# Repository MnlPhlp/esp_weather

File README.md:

# esp_weather
weather station powerd by an esp32 and rust.

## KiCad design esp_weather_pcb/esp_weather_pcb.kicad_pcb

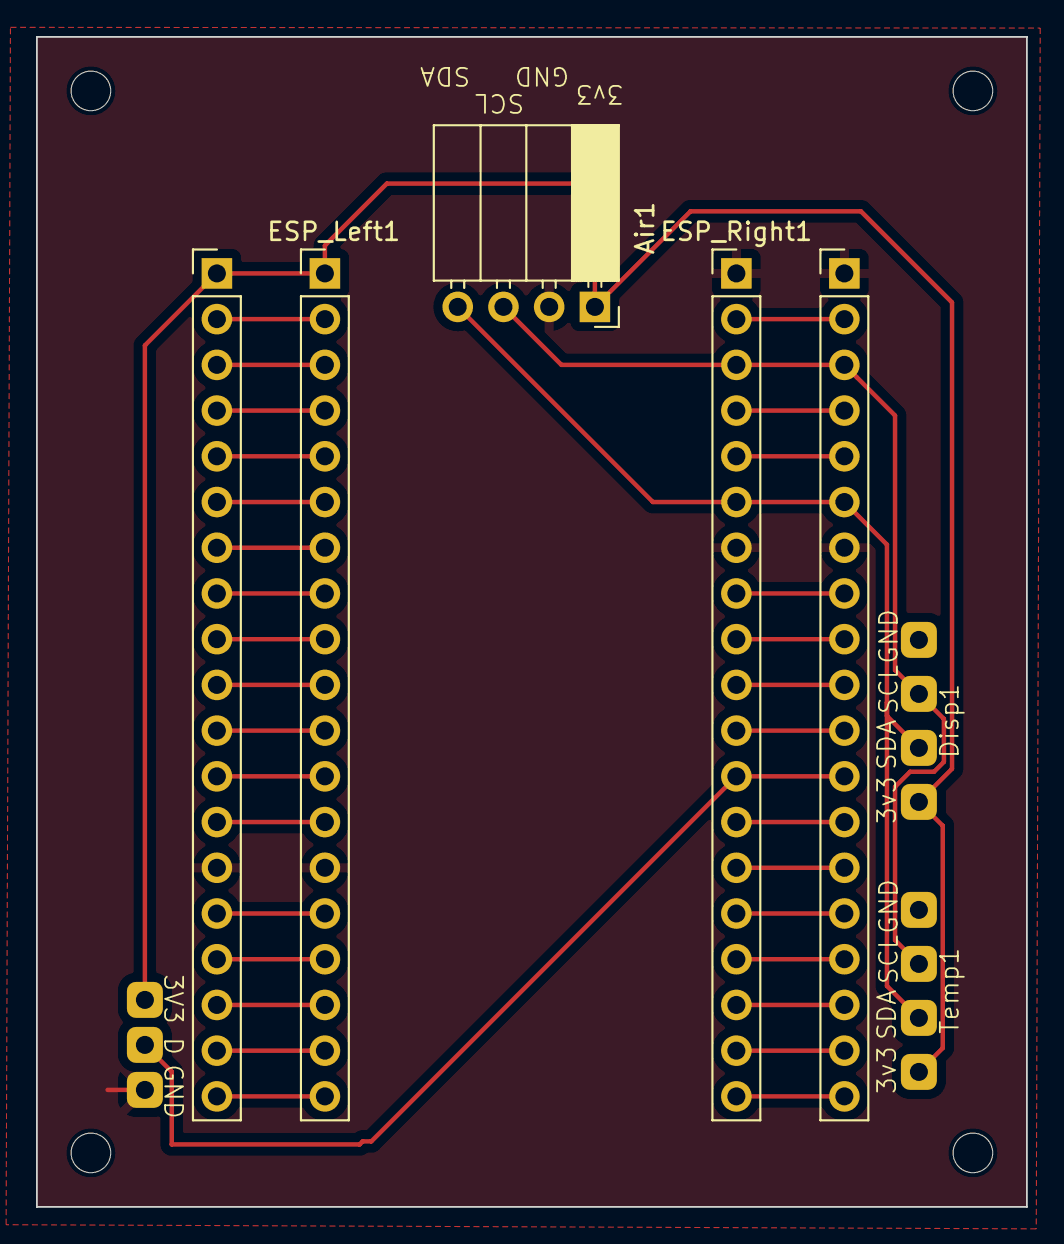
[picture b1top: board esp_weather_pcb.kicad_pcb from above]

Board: 2 copper layers, 55.0 x 65.0 mm, 8 parts (0 on the bottom side), 36 nets.

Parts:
Air1: PinSocket_1x04_P2.54mm_Horizontal
Disp1: I2C_Pads
ESP_Left1: esp32_38P_Left; esp32_38P_left
ESP_Right1: esp32_38P_Right; esp32_38P_right
Outside1: 3WIRE_Pads
Pads_Right1: esp32_38P_Right_Pads; esp32_38P_right_pads
Pads_left1: esp32_38P_Left_Pads; esp32_38P_left_Pads
Temp1: I2C_Pads

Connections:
3V3: Air1.1 (3V3), Disp1.1 (3V3), ESP_Left1.1 (3V3), Outside1.1 (3V3), Pads_left1.1 (3V3), Temp1.1 (3V3)
GND: Air1.2 (SDA), Disp1.4 (GND), ESP_Left1.14 (GND), ESP_Right1.32 (GND), ESP_Right1.38 (GND), Outside1.3 (GND), Pads_Right1.32 (GND), Pads_Right1.38 (GND), Pads_left1.14 (GND), Temp1.4 (GND)
unnamed: ESP_Left1.19 (5V), Pads_left1.19 (5V)
unnamed: ESP_Left1.2 (EN), Pads_left1.2 (EN)
unnamed: ESP_Left1.18 (FLASH_CMD), Pads_left1.18 (FLASH_CMD)
unnamed: ESP_Left1.16 (FLASH_D2), Pads_left1.16 (FLASH_D2)
unnamed: ESP_Left1.17 (FLASH_D3), Pads_left1.17 (FLASH_D3)
unnamed: ESP_Left1.13 (P12), Pads_left1.13 (P12)
unnamed: ESP_Left1.15 (P13), Pads_left1.15 (P13)
unnamed: ESP_Left1.12 (P14), Pads_left1.12 (P14)
unnamed: ESP_Left1.9 (P25), Pads_left1.9 (P25)
unnamed: ESP_Left1.10 (P26), Pads_left1.10 (P26)
unnamed: ESP_Left1.11 (P27), Pads_left1.11 (P27)
unnamed: ESP_Left1.7 (P32), Pads_left1.7 (P32)
unnamed: ESP_Left1.8 (P33), Pads_left1.8 (P33)
unnamed: ESP_Left1.5 (P34), Pads_left1.5 (P34)
unnamed: ESP_Left1.6 (P35), Pads_left1.6 (P35)
unnamed: ESP_Left1.3 (P36), Pads_left1.3 (P36)
unnamed: ESP_Left1.4 (P39), Pads_left1.4 (P39)
unnamed: ESP_Right1.20 (FLASH_CLK), Pads_Right1.20 (FLASH_CLK)
unnamed: ESP_Right1.21 (FLASH_D0), Pads_Right1.21 (FLASH_D0)
unnamed: ESP_Right1.22 (FLASH_D1), Pads_Right1.22 (FLASH_D1)
unnamed: ESP_Right1.25 (P0), Pads_Right1.25 (P0)
unnamed: ESP_Right1.24 (P2), Pads_Right1.24 (P2)
unnamed: ESP_Right1.26 (P4), Pads_Right1.26 (P4)
unnamed: ESP_Right1.29 (P5), Pads_Right1.29 (P5)
unnamed: ESP_Right1.23 (P15), Pads_Right1.23 (P15)
unnamed: ESP_Right1.28 (P17), Pads_Right1.28 (P17)
unnamed: ESP_Right1.30 (P18), Pads_Right1.30 (P18)
unnamed: ESP_Right1.31 (P19), Pads_Right1.31 (P19)
unnamed: ESP_Right1.37 (P23), Pads_Right1.37 (P23)
unnamed: ESP_Right1.34 (RX), Pads_Right1.34 (RX)
unnamed: ESP_Right1.35 (TX), Pads_Right1.35 (TX)
P16: ESP_Right1.27 (P16), Outside1.2 (D), Pads_Right1.27 (P16)
SCL: Air1.3 (SCL), Disp1.3 (SCL), ESP_Right1.36 (P22), Pads_Right1.36 (P22), Temp1.3 (SCL)
SDA: Air1.4 (GND), Disp1.2 (SDA), ESP_Right1.33 (P21), Pads_Right1.33 (P21), Temp1.2 (SDA)

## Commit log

2023-05-31 moved NOTICE
2023-06-01 got android to load rust library
2023-06-06 testing without messages and loop
2023-06-06 working version, with messages again
2023-06-06 started adding ble stuff in firmware
2023-06-06 more ble testing
2023-06-09 use common uuid values
2023-06-09 first working search
2023-06-09 blinking status led to tests tasks
2023-06-10 updated .gitattributes
2023-06-10 fixed warnings
2023-07-13 added Display. Started adding sensor
2023-07-14 made i2c and display shareable
2023-07-16 some experiments/tests
2023-07-19 new sensor and some changes
2023-07-26 made common part no_std compatible
2023-07-26 played more with no_std firmware
2023-08-01 new sensor
2023-08-01 adjusted app
2023-08-01 removed eclipse files
2023-09-11 started adding air sensor
2023-09-11 renamed
2023-09-11 added github action
2023-09-12 updated dependencies
2023-09-13 try contianer again
2023-09-13 added flutter caching
2023-09-21 new sensor and various fixes
2023-09-21 fixed app path
2023-09-21 remove apk form git
2023-10-30 fixed app build
2023-11-08 added pcb design
2023-11-08 updated pcb
